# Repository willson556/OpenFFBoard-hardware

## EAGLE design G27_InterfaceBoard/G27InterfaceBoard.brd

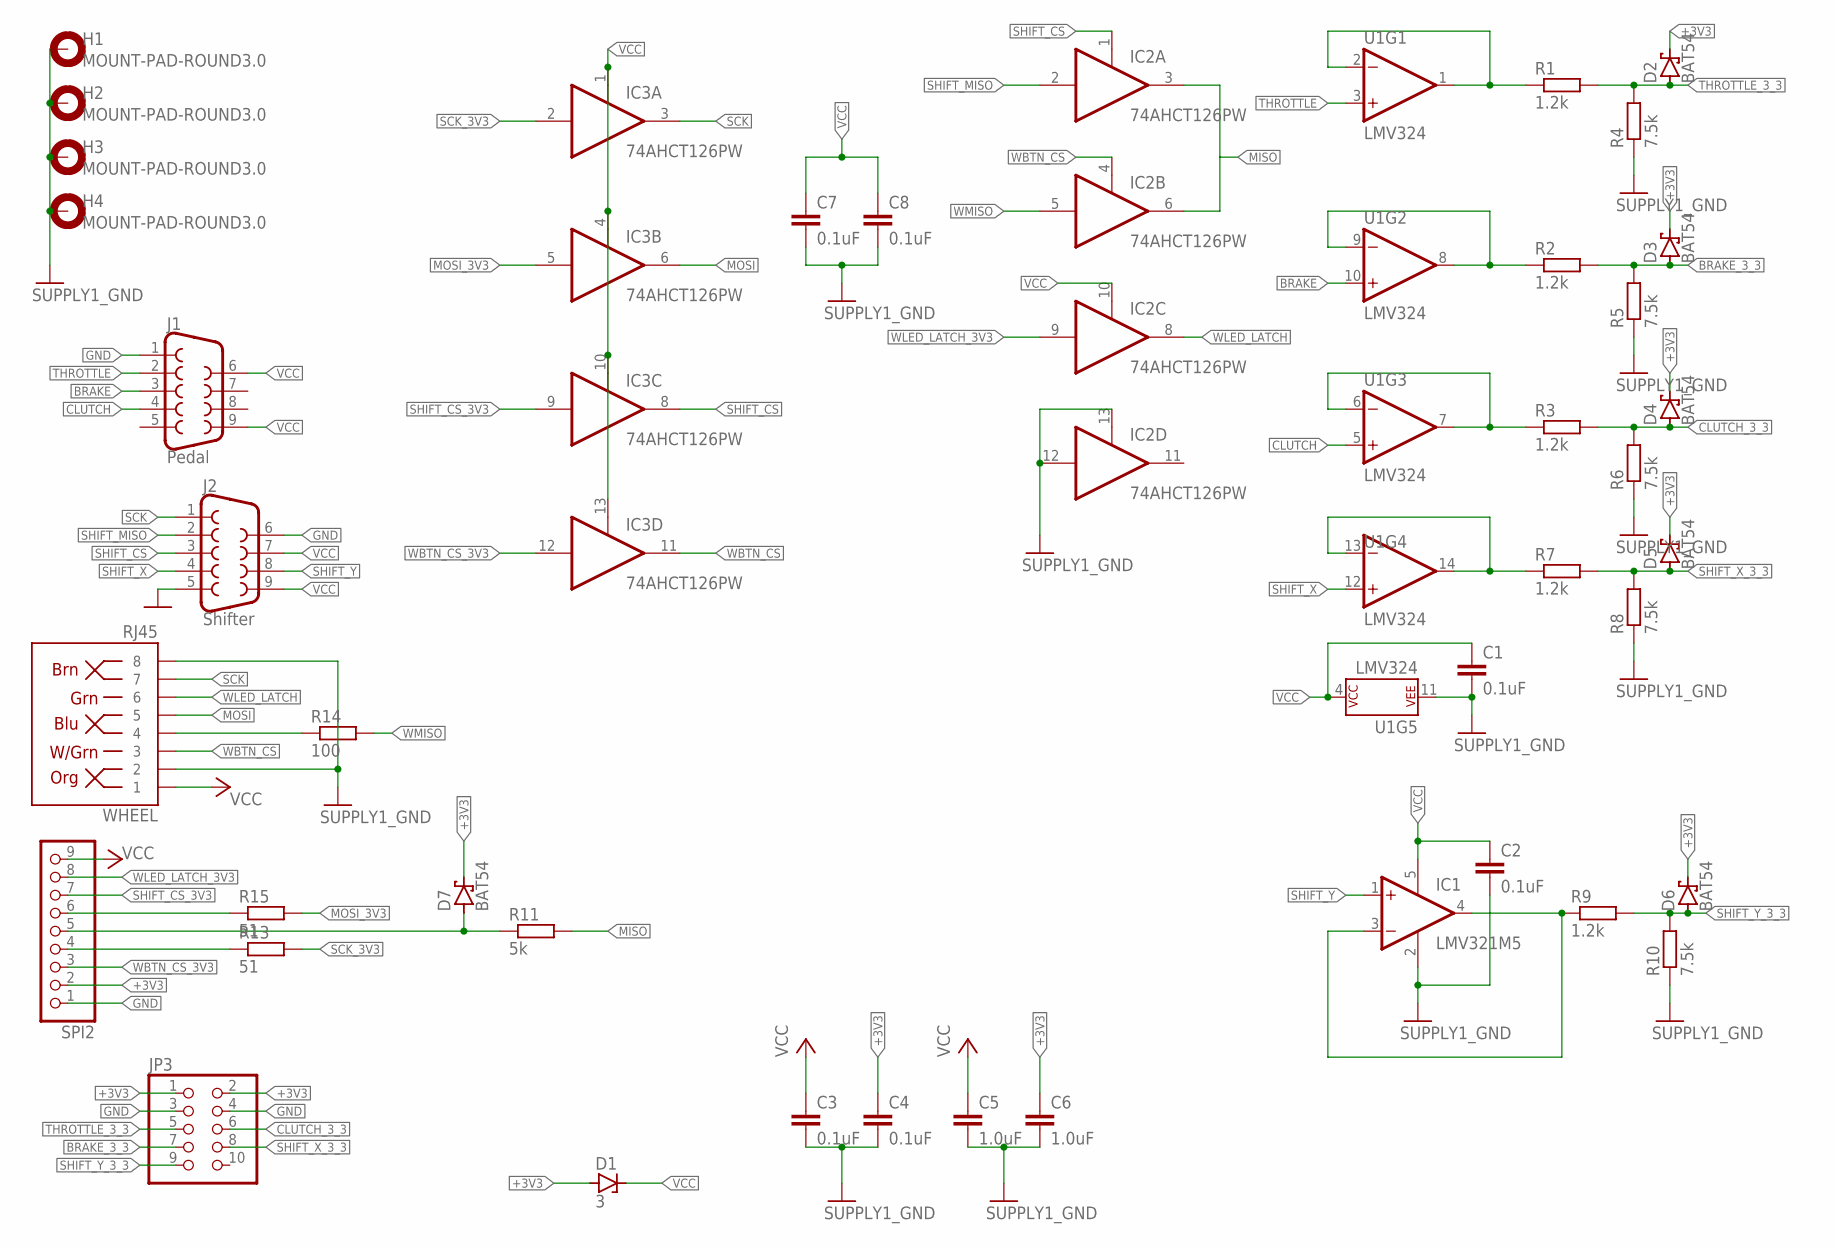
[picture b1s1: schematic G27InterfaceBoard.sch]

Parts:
C1, C2: 0.1uF; RESISTOR_C0603
C3, C4: 0.1uF; C0805
C5, C6: 1.0uF; C0805
C7, C8: 0.1uF; C0603
D1: 3; SOT23
D2, D3, D4, D5, D6, D7: BAT54; SOT23
H1, H2, H3, H4: MOUNT-PAD-ROUND3.0; 3,0-PAD
IC1: LMV321M5; SOT23-5
IC2, IC3: 74AHCT126PW; TSSOP14
J1: Pedal; DB9
J2: Shifter; DB9_MALE
JP3: PINHEAD_PINHD-2X5; PINHEAD_2X05
R1, R2, R3, R7, R9: 1.2k; R0603
R4, R5, R6, R8, R10: 7.5k; R0603
R11: 5k; R0603
R13, R15: 51; R0603
R14: 100; R0603
SPI2: PINHD-1X9; 1X09
U1: LMV324; SO14
WHEEL: RJ45; RJ45-8

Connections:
+3V3: C4.1, C6.1, D1.1 (A), D2.3 (C), D3.3 (C), D4.3 (C), D5.3 (C), D6.3 (C), D7.3 (C), JP3.1, JP3.2, SPI2.2
BRAKE: J1.3, U1.10 (+IN)
BRAKE_3_3: D3.1 (A), JP3.7, R2.2, R5.2
CLUTCH: J1.4, U1.5 (+IN)
CLUTCH_3_3: D4.1 (A), JP3.6, R3.2, R6.2
GND: C1.2, C2.2, C3.2, C4.2, C5.2, C6.2, C7.2, C8.2, H1.B3,0, H2.B3,0, H3.B3,0, H4.B3,0, IC1.2 (V-), IC2.7 (GND), IC2.12 (I), IC2.13 (OE), IC3.7 (GND), J1.1, J2.5, J2.6, JP3.3, JP3.4, R4.1, R5.1, R6.1, R8.1, R10.1, SPI2.1, U1.11 (P$V-), WHEEL.2, WHEEL.8
MISO: IC2.3 (O), IC2.6 (O), R11.2
MOSI: IC3.6 (O), WHEEL.5
MOSI_3V3: IC3.5 (I), R15.2
unnamed: R1.1, U1.1 (OUT), U1.2 (-IN)
unnamed: R7.1, U1.13 (-IN), U1.14 (OUT)
unnamed: IC1.3 (-IN), IC1.4 (OUT), R9.1
unnamed: D7.1 (A), R11.1, SPI2.5
unnamed: R2.1, U1.8 (OUT), U1.9 (-IN)
unnamed: R3.1, U1.6 (-IN), U1.7 (OUT)
unnamed: R13.1, SPI2.4
unnamed: R14.1, WHEEL.4
unnamed: R15.1, SPI2.6
SCK: IC3.3 (O), J2.1, WHEEL.7
SCK_3V3: IC3.2 (I), R13.2
SHIFT_CS: IC2.1 (OE), IC3.8 (O), J2.3
SHIFT_CS_3V3: IC3.9 (I), SPI2.7
SHIFT_MISO: IC2.2 (I), J2.2
SHIFT_X: J2.4, U1.12 (+IN)
SHIFT_X_3_3: D5.1 (A), JP3.8, R7.2, R8.2
SHIFT_Y: IC1.1 (+IN), J2.8
SHIFT_Y_3_3: D6.1 (A), JP3.9, R9.2, R10.2
THROTTLE: J1.2, U1.3 (+IN)
THROTTLE_3_3: D2.1 (A), JP3.5, R1.2, R4.2
VCC: C1.1, C2.1, C3.1, C5.1, C7.1, C8.1, D1.3 (C), IC1.5 (V+), IC2.10 (OE), IC2.14 (VCC), IC3.1 (OE), IC3.4 (OE), IC3.10 (OE), IC3.13 (OE), IC3.14 (VCC), J1.6, J1.9, J2.7, J2.9, SPI2.9, U1.4 (P$V+), WHEEL.1
WBTN_CS: IC2.4 (OE), IC3.11 (O), WHEEL.3
WBTN_CS_3V3: IC3.12 (I), SPI2.3
WLED_LATCH: IC2.8 (O), WHEEL.6
WLED_LATCH_3V3: IC2.9 (I), SPI2.8
WMISO: IC2.5 (I), R14.2

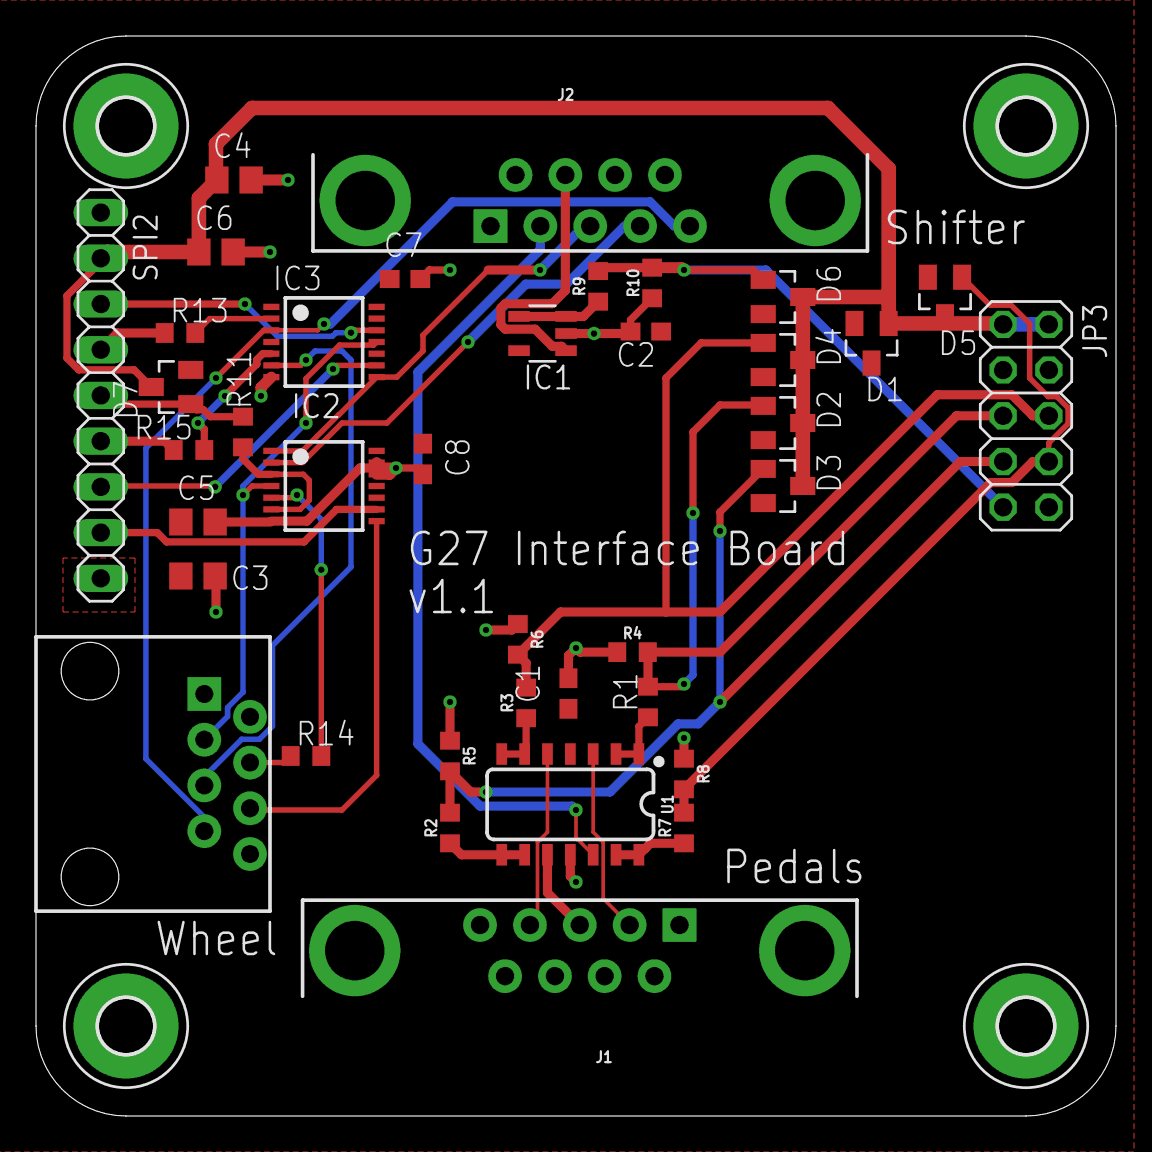
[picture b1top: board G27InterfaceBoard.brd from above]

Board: 2 copper layers, 60.0 x 60.0 mm, 42 parts (0 on the bottom side), 35 nets.

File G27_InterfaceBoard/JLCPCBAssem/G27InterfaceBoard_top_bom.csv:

Comment,Designator,Footprint,LCSC Part #
0.1uF,C1 C2,RESISTOR_C0603,
0.1uF,C3 C4,C0805,
1.0uF,C5 C6,C0805,
1.2k,R1 R2 R3 R7 R9,R0603,
3,D1,SOT23,
7.5k,R4 R5 R6 R8 R10,R0603,
51,R13 R15,R0603,
74HC126D,IC2,SO14,
100,R14,R0603,
LMV321M5,IC1,SOT23-5,
LMV324,U1,SO14,

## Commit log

2020-12-27 Started on G27 interface board.
2020-12-29 Modfications to board based on testing.
2020-12-30 Add some termination resistors to the SPI lines.
    A breadboarded version of this is now working with the G27 shifter
    and wheel simulataneously. LED control is not yet tested.
2021-01-13 G27InterfaceBoard v1.0 as ordered.
2021-01-17 Start of documentation.
2021-01-17 Add large components to BOM.
    Also, document more required tools.
2021-01-17 Add PCB costs to BOM.
2021-01-21 Add missing trace for wheel SCK.
2021-01-21 Bump board revision.
2021-01-23 Closer on G27 Interface v1.1:
    Use buffer to boost 3.3V signals from STM32 to 5V logic to buy
    better noise margin.
2021-01-23 Add additional filter caps.
2021-01-23 Add voltage clamps to signals that could go above 3.3V.
2021-01-23 Add better 5V, 3.3V, and GND connections.
2021-01-23 Connect shift power LED to ground.
2021-01-23 Minor silkscreen cleanup.
2021-01-23 G27InterfaceBoard v1.1 as ordered.

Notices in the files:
parts and their libraries:
SparkFun-Connectors: Licensing: Creative Commons ShareAlike 4.0 International - https://creativecommons.org/licenses/by-sa/4.0
